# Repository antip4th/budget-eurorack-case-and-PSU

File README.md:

# budget-eurorack-case-and-PSU #
This repo contains all files to build your own budget 84HP Eurorack case with intrgrated bus board, PSU and an optional filter PCB.  

I made this, because of my limited budget as a student, I could not afford 250+€ 84HP cases and power supplies. Also I liked the idea to build stuff myself :)  

The case features two MeanWell PSUs, each of which supplies up to 3 A. This should be more than enough for a 84 HP case. Only +-12 V supplies, no +5 V. The cost is about 150 € max. Less, if you already have some cables and screws.

To remove the PSU output voltage spikes, I designed a custom filter PCB. It consists of one pi-filter per PSU [(see schematic)](PSU_filter_pcb/docs/psu_filter_schematic.pdf). It also can be built nicely on prototyping board instead of the PCB.

## Performance
The power supply together with the filter PCB can offer up to 3 A per power rail. In my setup I could only test with up to 2 A per rail. Because of the series resistance in the filter, at 2 A the supply voltage drops by about 120 mV. If tuning the PSU output voltage to slightly more than 12 V, the resulting voltage is still close to +-12 V, even under load. Some ripple switching voltage at around 500 Hz remains with about 10 mV peak to peak.  

## BOM Case ## 
|Part  |Quantity  |Price  (Feb. 2026)  | Link |
|------|----------|--------------------|------|
| Mean Well RS-35-12 PSU | 2 | 13.36 € | [DigiKey](https://www.digikey.de/en/products/detail/mean-well-usa-inc/RS-35-12/7706181) |
| Doepfer Bus board V6 | 1 | 40 € | [Schneidersladen](https://schneidersladen.de/en/doepfer-a-100-bus-board-v6) |
| 84HP eurorack rails with lip | 2 | 9 € | [Schneidersladen](https://schneidersladen.de/en/divers-sb-rail-19-with-lip) |
| 84 HP eurorack rails without lip | 1 | 10 € | [Schneidersladen](https://schneidersladen.de/en/divers-sb-rail-19-without-lip) |
| M3 slider nuts| 1 | 10 € | [Schneidersladen](https://schneidersladen.de/en/frap-tools-sliding-nuts-100-pcs) |
| Module Screws | 1 | 6 € | [Schneidersladen](https://schneidersladen.de/en/frap-tools-m3x6-philips-panhead-screws-silver-100-pieces) |
| M5x25 or M5x20 socket head screws | 6 | Included with rails if you order from Schneidersladen | [Amazon](https://a.co/d/07VXTLld) |
| | | ~ 8.00 € otherwise | |
| M3x6 socket head screw | 6 | | | 
| M3x5 button head screw | 2-8 | | |
| AC Cold appliances built-in plug | 1 | ~ 8 € | [Amazon](https://amzn.eu/d/06RYOiwI) |
| 0.75 mm²/18 AWG silicone cable | 1 m | 13 € | [Amazon](https://amzn.eu/d/0fPG9uPr) |
| Insulated cable lugs | 1 | 7 € | [Amazon](https://amzn.eu/d/0cKYAwAh) |
| Fork wire terminals | 1 | 7 € | [Amazon](https://amzn.eu/d/0jiY2vDV) |
| 3D-printed parts | | 3 € | |
| some heatshrink tubing | | | |
| SUM | | ~ 150 € worst case | |  

## BOM Filter PCB ##
|Part  |Quantity  |Price  (Feb. 2026)  | Link |
|------|----------|--------------------|------|
| Low ESR electrolytic caps 1000 µF | 4 | 0.5 € | [reichelt](https://www.reichelt.com/de/en/shop/product/elko_radial_1000_f_25_v_105_low_esr_12_5x20_mm_rm_5-166391?search=RAD%2520LXZ%252025%252F1K0B&)|
| Ceramic caps 100 nF | 4 | 0.1 € | [reichelt](https://www.reichelt.com/de/en/shop/product/smd_multilayer_ceramic_capacitor_100_n_10_-22889?search=X7R-G1206%2520100n&) |
| Ferrite core inductor 10 μΗ | 2 | 1 € | [reichelt](https://www.reichelt.com/de/en/shop/product/vertical_inductor_09hcp_ferrite_10_h-138644?country=de&CCTYPE=private&LANGUAGE=en) |
| Custom PCB or prototyping board | 1 | ~15 € if you have the PCB manufactured | |
| SUM | | ~ 20 € | |

## Build Instructions

### PCB

The soldering process is quite straight forward. I went for solder pads instead of terminal blocks to minimize contact resistance. Because of the big copper planes, for soldering the wires, I had to turn my soldering iron up to 450 °C.

### Case

> [!CAUTION]
> This build requires wiring of mains power. Only work with mains voltage, if you know what you are doing!  
> Improper handling can cause electric shock, fire, or death. No liability is accepted for damage or injury.

1. The build starts with the wiring. The wire colors in this text correspond to the colors I used in my build and can be seen in the photos.
  1. Use the fork wire terminals to, connect the mains L (red), P (blue) and PE (green) terminals form the AC cold appliance socket with the respective terminals on both PSUs. The PSUs should be  connected to mains **in parallel**. You need to squeeze two cables into one cable lug.
  2. To get +-12 V outputs, the `-V` terminal of one of the PSUs is connected to the `+V` terminal of the other one. This node is the ground rail for the +-12 V outputs. I soldered both GND cables (black) onto the PCB's GND pad. If you don't use the PCB, directly crimp the bus board connector.
  3. The remaining `+V` output is the +12 V rail (yellow), and the remaining `-V` output is the -12 V rail (white). Either connect them to the PCB or crimp the connectors for the bus board directly.
  4. If you use the PCB, solder the cables on the output side and crimp the bus board connectors.

2. Once the wiring is done, put everything together in the PSU case. Fix the PSUs to the case with the two screws on the bottom side. **Use short screws (<= 5mm) for this or you risk pushing the screw against the PCB inside the PSU!**

3. Attach the lid parts and the rib parts to the rail **without lip**. Use some of the screws and slider nuts for later fixing the position of the parts on the rail. 

4. Attach the bus board to the rails with slider nuts. Put the ends of the PSUs into the ribs. Close everything up. Attach the side panels and the other rails and you're done!

## License

The contents of this repo are available under CERN OHL-S license.

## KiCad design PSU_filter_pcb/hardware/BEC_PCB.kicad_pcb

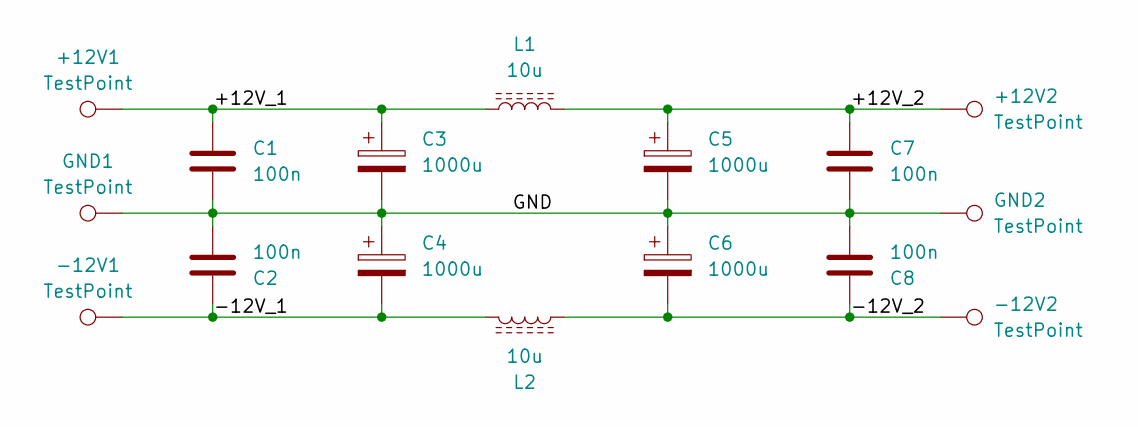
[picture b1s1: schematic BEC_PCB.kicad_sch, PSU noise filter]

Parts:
+12V1, +12V2: TestPoint; WirePad_L6mm_W4mm
-12V1, -12V2: TestPoint; WirePad_L6mm_W4mm
C1, C2, C7, C8: 100n; C_1206_3216Metric_Pad1.33x1.80mm_HandSolder
C3, C4, C5, C6: 1000u; CP_Radial_D13.0mm_P5.00mm
GND1, GND2: TestPoint; WirePad_L6mm_W4mm
L1, L2: 10u; L_Radial_D12.5mm_P7.00mm_Fastron_09HCP

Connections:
/+12V_1: +12V1.1, C1.1, C3.1, L1.1
/+12V_2: +12V2.1, C5.1, C7.1, L1.2
/-12V_1: -12V1.1, C2.1, C4.2, L2.1
/-12V_2: -12V2.1, C6.2, C8.1, L2.2
/GND: C1.2, C2.2, C3.2, C4.1, C5.2, C6.1, C7.2, C8.2, GND1.1, GND2.1

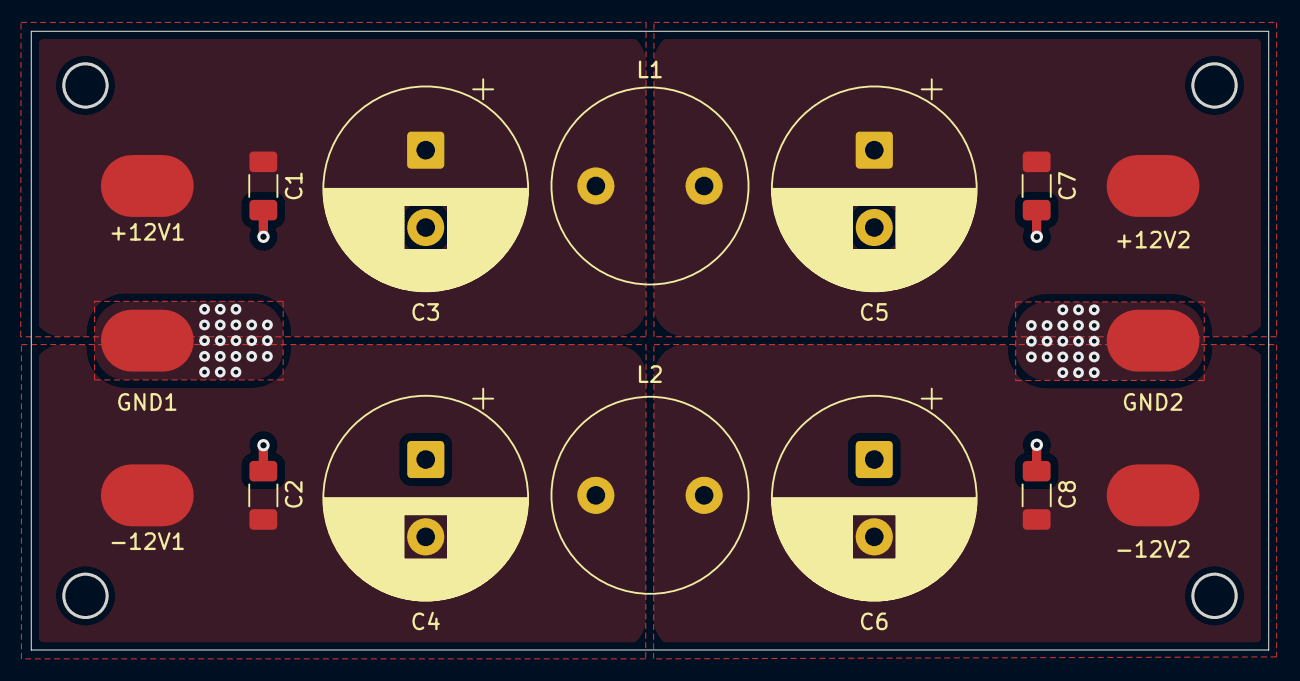
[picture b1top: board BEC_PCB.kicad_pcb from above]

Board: 2 copper layers, 79.9 x 39.9 mm, 16 parts (0 on the bottom side), 5 nets.

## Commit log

2024-10-03 Created BOM
2026-03-02 Enhance README with detailed project description
    Updated project description for clarity and detail.
2026-03-02 Revise BOM entries and links in README
    Updated the Bill of Materials (BOM) with corrected items and links.
2026-03-02 Revise BOM with updated prices and links
    Updated the Bill of Materials (BOM) with new links and pricing.
2026-03-02 Enhance README with filter PCB and build details
    Updated README to include optional filter PCB and additional details about the build and BOM.
2026-03-02 Update README with bus board and filter PCB details
2026-03-02 Fix formatting and headings in README.md
2026-03-02 Update README with BOM and cost details
    Added details about the cost and components for the Eurorack case and filter PCB.
2026-03-02 Fix formatting and add new components to README
2026-03-02 Update BOM Filter PCB with prices and links
2026-03-02 Add summary row for total cost in README
2026-03-03 Fix typo in README about case features
    Corrected a typo in the description of the case features.
2026-03-03 Clarify cost for custom PCB in README
    Updated the cost description for the custom PCB or prototyping board.
2026-03-03 Update README for clarity and grammar fixes
    Corrected grammatical errors and improved clarity in the README.
2026-03-03 upload project files
2026-03-03 add images
2026-03-04 upload images
2026-03-04 fix readme
2026-03-04 edit readme
2026-03-04 update build instructions
2026-03-04 changed filename
2026-03-04 add schematic pdf
2026-03-04 renaming
2026-03-04 add bom csv
2026-03-04 add CERN-OHL S license
2026-03-04 add license note to readme
2026-03-04 removed rail STLs
2026-03-04 restructure readme
2026-03-06 fix typo
